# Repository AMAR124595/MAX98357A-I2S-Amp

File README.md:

# MAX98357A I2S Class-D Audio Amplifier 

Custom 2-layer PCB design for a compact **mono I2S digital audio amplifier** based on the **MAX98357AETE+T**.

This board provides a complete digital-to-speaker solution with an integrated DAC and filterless Class-D output stage, intended for embedded and production-oriented audio systems.

---

## Overview

The MAX98357A integrates:

* Digital I2S audio interface
* Internal DAC
* High-efficiency Class-D amplifier
* Automatic clock detection

This PCB is designed for direct integration with:

* ESP32
* STM32
* Raspberry Pi
* Any MCU supporting I2S output

---

## Main IC

**Part Number:** MAX98357AETE+T
**Package:** TQFN-16 (3mm × 3mm, 0.5mm pitch, exposed pad)
**Manufacturer:** Analog Devices / Maxim Integrated

### Key Characteristics

* Supply range: 2.7V – 5.5V
* Output power: up to 3.2W into 4Ω @ 5V
* Sample rate: 8kHz – 96kHz
* Differential BTL output
* > 90% typical efficiency

---

## Technical Specifications

| Parameter             | Value              |
| --------------------- | ------------------ |
| Supply Voltage        | 2.7V – 5.5V        |
| Recommended Operation | 5V                 |
| Output Power          | 3.2W @ 4Ω          |
| Output Type           | Differential (BTL) |
| Audio Interface       | I2S                |
| PCB Layers            | 2-Layer            |

---

## Interface

### I2S Input Header (J2 – 1x7, 2.54mm)

| Pin   | Function    |
| ----- | ----------- |
| VIN   | 5V Supply   |
| GND   | Ground      |
| BCLK  | Bit Clock   |
| LRCLK | Word Select |
| DIN   | Serial Data |
| SD    | Shutdown    |
| GAIN  | Gain Select |

### Speaker Output (J1 – 3.5mm Terminal Block)

* OUTP
* OUTN

⚠️ Speaker must be connected between OUTP and OUTN.
Do not connect either output to ground.

---

## Bill of Materials

| Reference | Value                 | Footprint                | Qty |
| --------- | --------------------- | ------------------------ | --- |
| U1        | MAX98357A             | TQFN-16-1EP_3x3mm_P0.5mm | 1   |
| C1        | 22pF                  | 0603                     | 1   |
| C2        | 10µF                  | 0603                     | 1   |
| C3        | 0.1µF                 | 0402                     | 1   |
| C4, C5    | 220pF                 | 0402                     | 2   |
| FB1, FB2  | 100Ω @100MHz, 3A      | 0603                     | 2   |
| R1        | 1MΩ                   | 0603                     | 1   |
| J1        | Terminal Block 3.5mm  | —                        | 1   |
| J2        | 1x7 Pin Header 2.54mm | —                        | 1   |
| TP1       | OUTN Test Pad         | 1mm Pad                  | 1   |
| TP2       | OUTP Test Pad         | 1mm Pad                  | 1   |

Full fabrication files are available in the repository.

---

## PCB Design Notes

### Power & Decoupling

* 10µF bulk capacitor near VIN entry
* 0.1µF placed close to VDD
* Solid ground plane implemented
* Exposed pad tied to GND with multiple vias

### Signal Integrity

* Short I2S routing
* Differential outputs routed symmetrically
* Wide copper traces for speaker current

### EMI Control

* Ferrite beads on both output lines
* 220pF capacitors for high-frequency suppression
* Minimized switching loop area

---

## Validation Procedure

1. Apply 5V supply without speaker → verify idle current.
2. Probe BCLK, LRCLK, and DIN using oscilloscope.
3. Connect 4Ω speaker and inject test tone.
4. Verify clean differential waveform.
5. Monitor IC temperature at high output levels.

---

## Repository Contents

* Documentation
* Schematic files
* PCB layout files
* BOM

---

## Manufacturing Notes

* Reflow soldering recommended for TQFN package.
* Proper stencil aperture for exposed pad.
* Ensure adequate thermal grounding.
* Ferrite beads must support ≥3A peak current.
* Avoid thermal relief on exposed pad.

---

## Applications

* Embedded audio systems
* Smart speakers
* IoT voice modules
* Portable digital audio devices
* Industrial alert systems

---

## References

* [https://www.analog.com/media/en/technical-documentation/data-sheets/MAX98357A-MAX98357B.pdf](https://www.analog.com/media/en/technical-documentation/data-sheets/MAX98357A-MAX98357B.pdf)
* [https://www.analog.com/media/en/technical-documentation/data-sheets/MAX98357DEVTQFN-MAX98357EVSYSTQFN.pdf](https://www.analog.com/media/en/technical-documentation/data-sheets/MAX98357DEVTQFN-MAX98357EVSYSTQFN.pdf)
* [https://www.adafruit.com/product/3006](https://www.adafruit.com/product/3006)
* [https://robu.in/wp-content/uploads/2021/10/MAX98357AETET.pdf](https://robu.in/wp-content/uploads/2021/10/MAX98357AETET.pdf)

---

## Author

**Amar Gangadhar**

Electronics Engineer | Embedded Systems Designer |  Embedded Firmware Developer | PCB Design Engineer

---

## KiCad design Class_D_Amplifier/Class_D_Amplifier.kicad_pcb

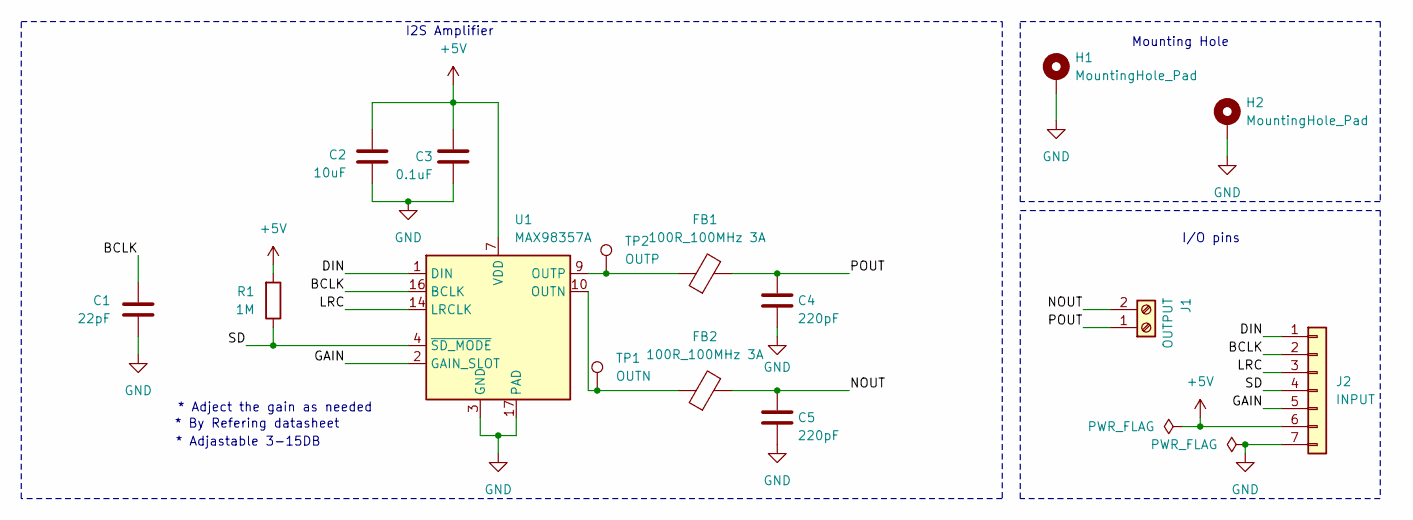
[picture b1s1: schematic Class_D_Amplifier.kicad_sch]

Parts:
C1: 22pF; C_0603_1608Metric_Pad1.08x0.95mm_HandSolder
C2: 10uF; C_0603_1608Metric_Pad1.08x0.95mm_HandSolder
C3: 0.1uF; C_0402_1005Metric_Pad0.74x0.62mm_HandSolder
C4, C5: 220pF; C_0402_1005Metric_Pad0.74x0.62mm_HandSolder
FB1, FB2: 100R_100MHz 3A; L_0603_1608Metric_Pad1.05x0.95mm_HandSolder
H1, H2: MountingHole_Pad; MountingHole_3.2mm_M3_Pad_Via
J1: OUTPUT; TerminalBlock_Phoenix_PT-1,5-2-3.5-H_1x02_P3.50mm_Horizontal
J2: INPUT; PinHeader_1x07_P2.54mm_Vertical
R1: 1M; R_0603_1608Metric_Pad0.98x0.95mm_HandSolder
TP1: OUTN; TestPoint_Pad_D1.0mm
TP2: OUTP; TestPoint_Pad_D1.0mm
U1: MAX98357A; TQFN-16-1EP_3x3mm_P0.5mm_EP1.23x1.23mm

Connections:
+5V: C2.1, C3.1, J2.6, R1.2, U1.7 (VDD), U1.8 (VDD)
/BCLK: C1.1, J2.2, U1.16 (BCLK)
/DIN: J2.1, U1.1 (DIN)
/GAIN: J2.5, U1.2 (GAIN_SLOT)
/LRC: J2.3, U1.14 (LRCLK)
/NOUT: C5.1, FB2.2, J1.2
/POUT: C4.1, FB1.2, J1.1
/SD: J2.4, R1.1, U1.4 (~SD_MODE)
GND: C1.2, C2.2, C3.2, C4.2, C5.2, H1.1, H2.1, J2.7, U1.3 (GND), U1.11 (GND), U1.15 (GND), U1.17 (PAD)
unnamed: FB2.1, TP1.1, U1.10 (OUTN)
unnamed: FB1.1, TP2.1, U1.9 (OUTP)

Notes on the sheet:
I/O pins
Mounting Hole
* Adjastable 3-15DB
* By Refering datasheet
* Adject the gain as needed
I2S Amplifier

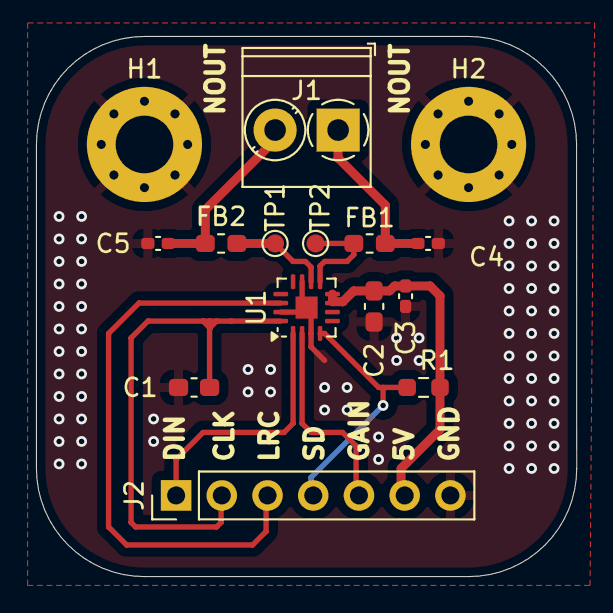
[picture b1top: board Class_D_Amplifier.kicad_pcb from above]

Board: 2 copper layers, 30.0 x 30.0 mm, 15 parts (0 on the bottom side), 11 nets.

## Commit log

2026-02-20 MAX98357A I2S Class D Amplifier
2026-02-20 Stop tracking backup and cache files
2026-02-20 Deleted some files
